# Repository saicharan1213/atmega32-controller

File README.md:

# atmega32-controller
1. use the ".hex" file to upload the code to microcontroller board<br />
2. check the file with ".simu" extension for circuit schematic<br />
3. ".brd" and ".sch" files are done using EAGLE. these files are PCB design

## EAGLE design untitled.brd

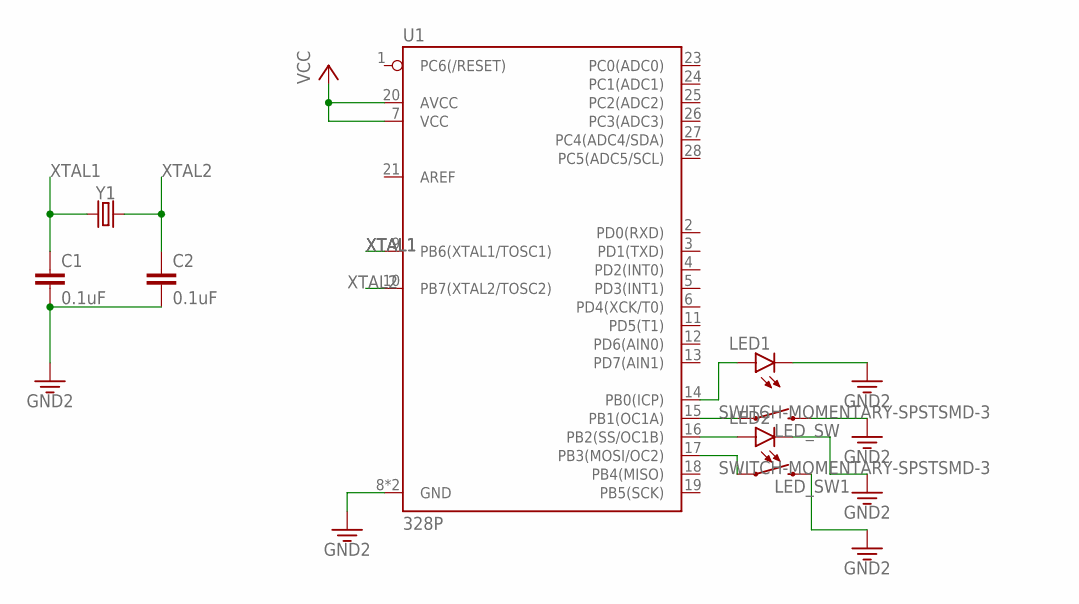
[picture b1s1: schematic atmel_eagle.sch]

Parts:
C1, C2: 0.1uF; CAP-PTH-SMALL-KIT
LED1, LED2: LED10MM
LED_SW, LED_SW1: SWITCH-MOMENTARY-SPSTSMD-3; TACTILE_SWITCH_SMD-3
U1: 328P; DIP28
Y1: CRYSTALPTH-HC49US; HC49US

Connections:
3.3V: C1.2, C2.2, LED1.K (C), LED2.K (C), LED_SW.4 (2), LED_SW1.4 (2), U1.8 (GND), U1.22 (GND)
unnamed: LED_SW.1, U1.15 (PB1(OC1A))
unnamed: LED1.A, U1.14 (PB0(ICP))
unnamed: LED2.A, U1.16 (PB2(SS/OC1B))
unnamed: LED_SW1.1, U1.17 (PB3(MOSI/OC2))
VCC: U1.7 (VCC), U1.20 (AVCC)
XTAL1: C1.1, U1.9 (PB6(XTAL1/TOSC1)), Y1.1
XTAL2: C2.1, U1.10 (PB7(XTAL2/TOSC2)), Y1.2

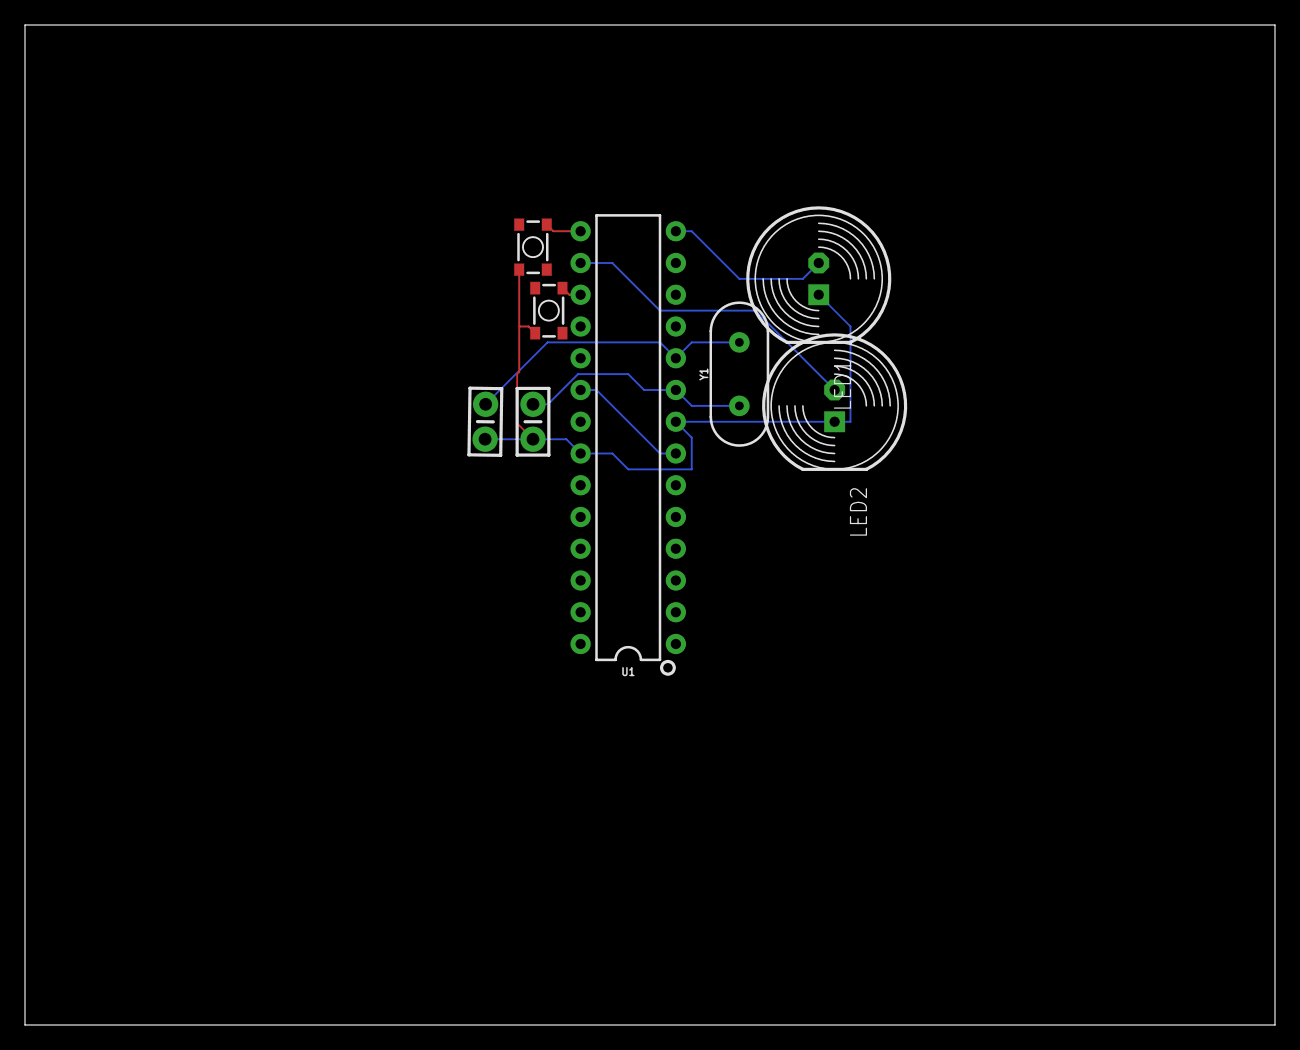
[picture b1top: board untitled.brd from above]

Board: 2 copper layers, 100.0 x 80.0 mm, 8 parts (0 on the bottom side), 8 nets.

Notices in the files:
parts and their libraries:
SparkFun-PowerSymbols: Licensing: Creative Commons ShareAlike 4.0 International - https://creativecommons.org/licenses/by-sa/4.0
